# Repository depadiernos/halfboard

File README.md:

# Halfboard

PCB:

Halfboard with Choc V1 switches:

Layout:

If using a nice!nano, you can download the firmware here: https://github.com/depadiernos/zmk-config/blob/master/firmware.zip

The zmk-config repo is here: https://github.com/depadiernos/zmk-config

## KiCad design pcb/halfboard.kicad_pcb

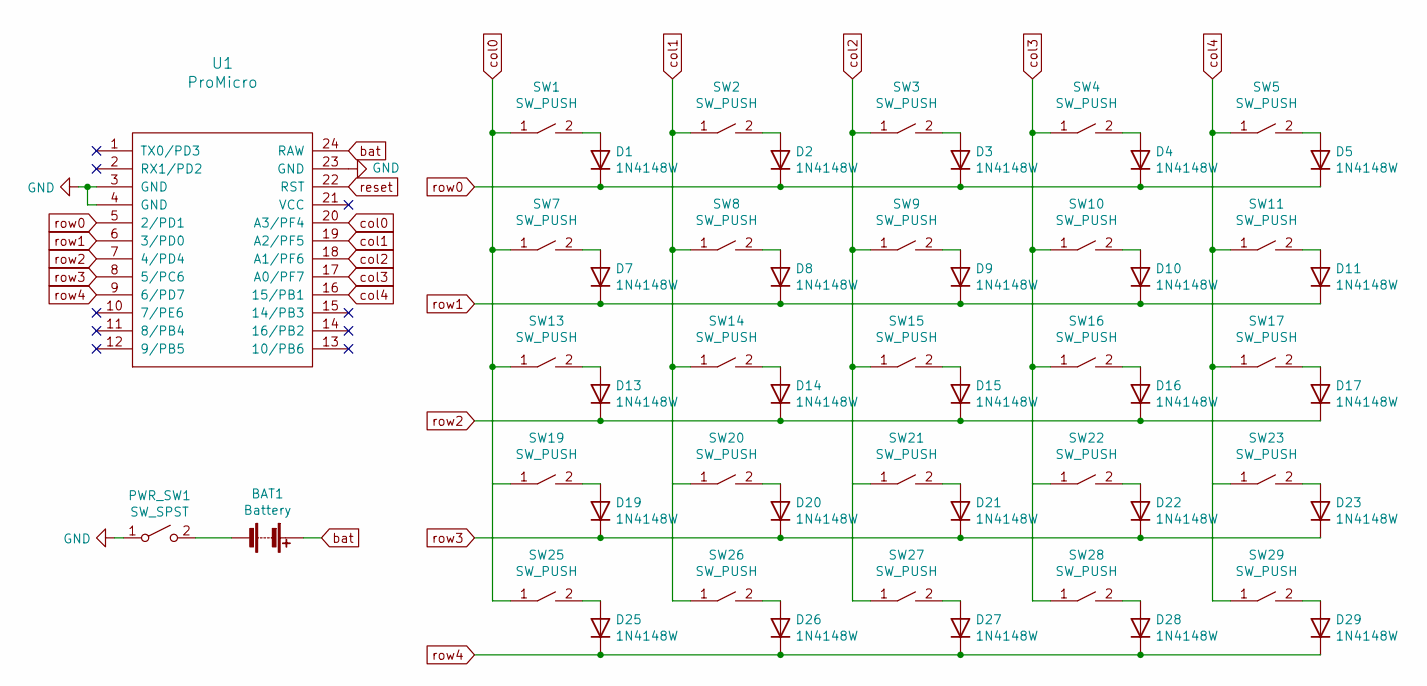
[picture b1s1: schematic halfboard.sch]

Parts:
BAT1: Battery; PinHeader_1x02_P2.54mm_Vertical
D1, D2, D3, D4, D5, D7, D8, D9, D10, D11, D13, D14, D15, D16, D17, D19, D20, D21, D22, D23, D25, D26, D27, D28, D29: 1N4148W; Diode-dual
PWR_SW1: SW_SPST; SW_SPDT_PCM12
SW1, SW2, SW3, SW4, SW5, SW7, SW8, SW9, SW10, SW11, SW13, SW14, SW15, SW16, SW17, SW19, SW20, SW21, SW22, SW23, SW25, SW26, SW27, SW28, SW29: SW_PUSH; MX-ALPs-PG1350-LED-FLIP
U1: ProMicro; ArduinoProMicro-TopSide

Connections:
GND: PWR_SW1.1 (A), U1.3 (GND), U1.4 (GND), U1.23 (GND)
unnamed: BAT1.2 (-), PWR_SW1.2 (B)
unnamed: D1.2 (A), SW1.2
unnamed: D2.2 (A), SW2.2
unnamed: D3.2 (A), SW3.2
unnamed: D4.2 (A), SW4.2
unnamed: D5.2 (A), SW5.2
unnamed: D7.2 (A), SW7.2
unnamed: D8.2 (A), SW8.2
unnamed: D9.2 (A), SW9.2
unnamed: D10.2 (A), SW10.2
unnamed: D11.2 (A), SW11.2
unnamed: D13.2 (A), SW13.2
unnamed: D14.2 (A), SW14.2
unnamed: D15.2 (A), SW15.2
unnamed: D16.2 (A), SW16.2
unnamed: D17.2 (A), SW17.2
unnamed: D19.2 (A), SW19.2
unnamed: D20.2 (A), SW20.2
unnamed: D21.2 (A), SW21.2
unnamed: D22.2 (A), SW22.2
unnamed: D23.2 (A), SW23.2
unnamed: D25.2 (A), SW25.2
unnamed: D26.2 (A), SW26.2
unnamed: D27.2 (A), SW27.2
unnamed: D28.2 (A), SW28.2
unnamed: D29.2 (A), SW29.2
bat: BAT1.1 (+), U1.24 (RAW)
col0: SW1.1, SW7.1, SW13.1, SW19.1, SW25.1, U1.20 (A3/PF4)
col1: SW2.1, SW8.1, SW14.1, SW20.1, SW26.1, U1.19 (A2/PF5)
col2: SW3.1, SW9.1, SW15.1, SW21.1, SW27.1, U1.18 (A1/PF6)
col3: SW4.1, SW10.1, SW16.1, SW22.1, SW28.1, U1.17 (A0/PF7)
col4: SW5.1, SW11.1, SW17.1, SW23.1, SW29.1, U1.16 (15/PB1)
reset: U1.22 (RST)
row0: D1.1 (K), D2.1 (K), D3.1 (K), D4.1 (K), D5.1 (K), U1.5 (2/PD1)
row1: D7.1 (K), D8.1 (K), D9.1 (K), D10.1 (K), D11.1 (K), U1.6 (3/PD0)
row2: D13.1 (K), D14.1 (K), D15.1 (K), D16.1 (K), D17.1 (K), U1.7 (4/PD4)
row3: D19.1 (K), D20.1 (K), D21.1 (K), D22.1 (K), D23.1 (K), U1.8 (5/PC6)
row4: D25.1 (K), D26.1 (K), D27.1 (K), D28.1 (K), D29.1 (K), U1.9 (6/PD7)

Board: 2 copper layers, 53 parts (0 on the bottom side), 38 nets, no tracks yet.

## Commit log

2021-01-06 Add kicad and gerber files.
2021-01-06 add pcb screenshot
2021-01-06 add screenshot of pcb
2021-01-06 add ground planes
2021-01-06 add option to flip the board
2021-01-06 update screenshot
2021-01-06 Update PCB
2021-01-07 Add a bottom plate with mcu cut out
2021-01-07 update gerber files
2021-01-07 move gerber files to a folder
2021-01-08 update switch footpring to support v2
2021-01-08 update switch footprint to support Choc v2
2021-01-08 switch to a universal switch footprint. supports mx, alps, choc v1/v2.
2021-01-08 clean footprint
2021-01-08 tweak universal footprint a bit more
2021-01-10 route traces and fix spacing of footprints
2021-01-10 various tweaks
2021-01-10 remove unused footprints
2021-01-10 remove some unneeded silkscreen
2021-01-10 update gerber files again
2021-01-12 rotated the switch footprint
2021-01-15 add halfboard mockup image
2021-01-15 add mockup image
2021-01-18 upload default layout
2021-01-18 set width
2021-01-19 update layout img
2021-01-19 move battery/switch and correct polarity
2021-01-19 update gerber files and pcb screenshot
2021-01-19 remove front silkscreens
2021-01-19 update gerber zip and screenshot
2021-01-19 update layout and remove more silkscreen
2021-01-19 add gitignore to clean repo up a bit
2021-01-19 ignore common cache and backup files
2021-01-19 non-X2 halfboard-bottom gerber files
2021-01-19 add CERN OPEN HARDWARE LICENSE V2 strongly-reciprocal variant
2021-01-20 restructure project and add a top plate
2021-01-20 update pcb gerber files
2021-01-20 update top plate gerber files
2021-01-22 update footprint for better fit
2021-01-23 redo routing using freerouting
2021-01-23 update pcb image
2021-01-25 create schematics and assign footprints in pcb
2021-01-25 finish pcb using new schematics
2021-01-26 add ground plane
2021-01-26 update pcb render
2021-01-28 update layout image ... again
2021-02-03 5x4 layout instead of 6x4
